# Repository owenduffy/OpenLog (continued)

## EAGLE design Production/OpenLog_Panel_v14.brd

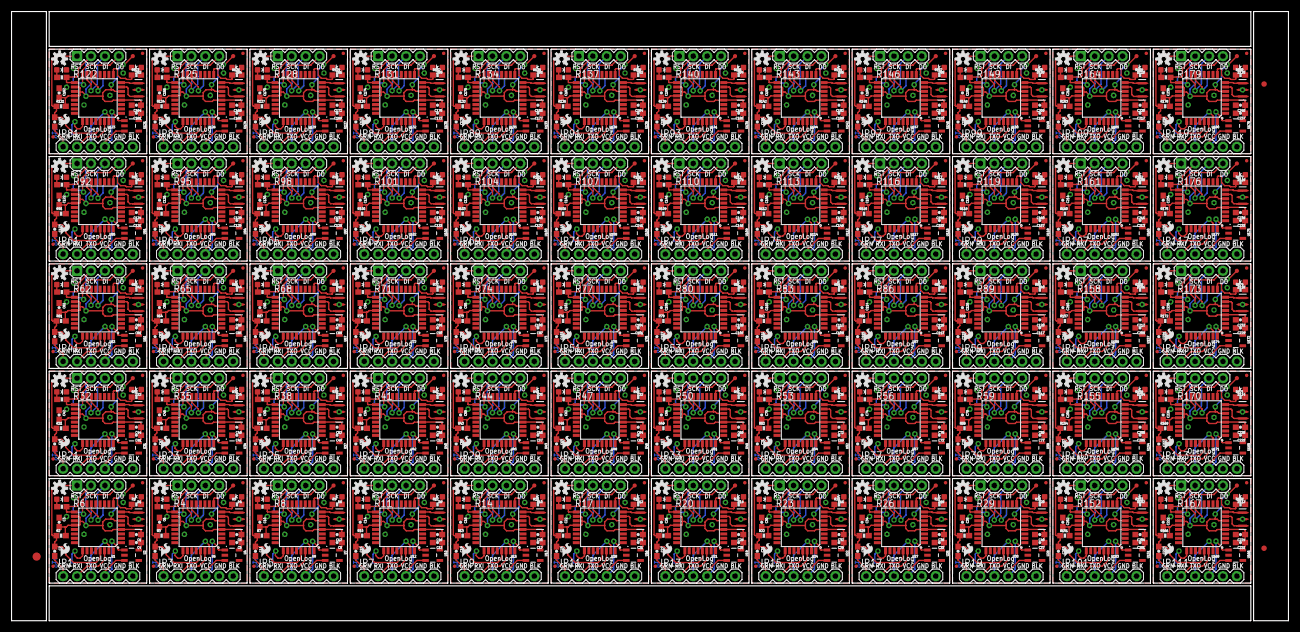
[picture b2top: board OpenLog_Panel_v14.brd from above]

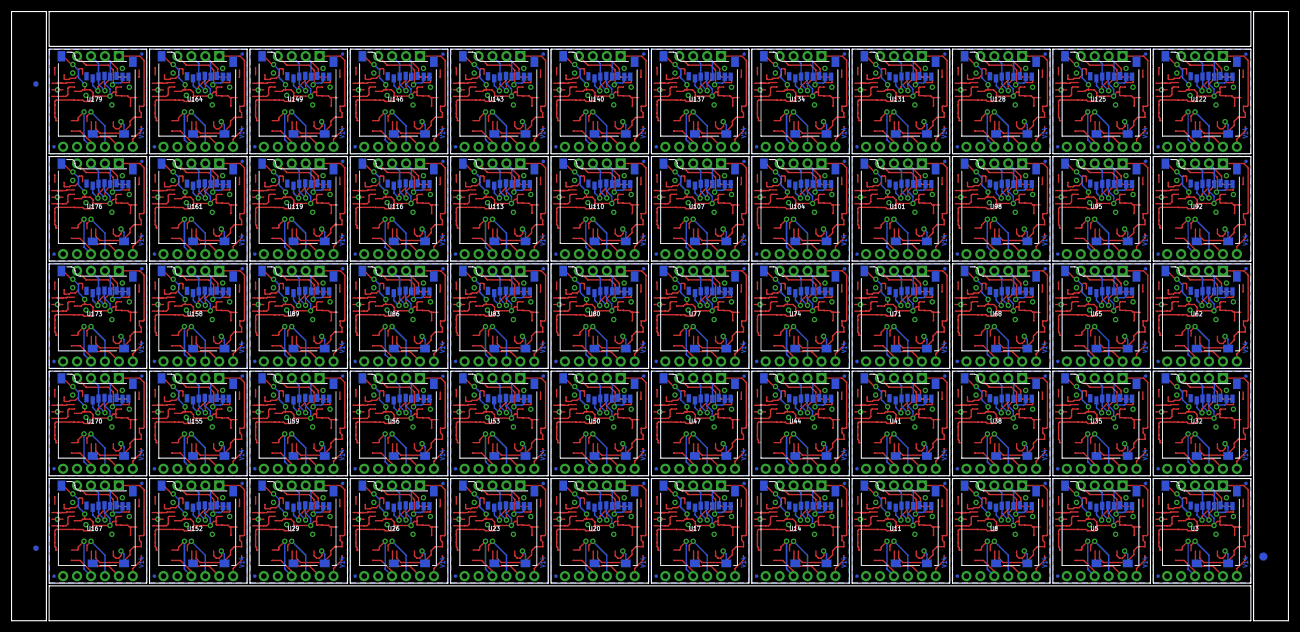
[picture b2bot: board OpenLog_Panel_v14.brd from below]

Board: 2 copper layers, 232.7 x 111.0 mm, 1326 parts (183 on the bottom side), 1020 nets.

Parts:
C1, C8, C12, C16, C20, C24, C28, C32, C36, C40, C44, C48, C52, C56, C60, C64, C68, C72, C76, C80, C84, C88, C92, C96, C100, C104, C108, C112, C116, C120, C124, C128, C132, C136, C140, C144, C148, C152, C156, C160, C164, C168, C172, C176, C180, C184, C188, C192, C196, C200, C204, C208, C212, C216, C220, C224, C228, C232, C236, C240: 1.0uF; 0603-CAP
C2, C3, C4, C5, C6, C7, C9, C10, C11, C13, C14, C15, C17, C18, C19, C21, C22, C23, C25, C26, C27, C29, C30, C31, C33, C34, C35, C37, C38, C39, C41, C42, C43, C45, C46, C47, C49, C50, C51, C53, C54, C55, C57, C58, C59, C61, C62, C63, C65, C66, C67, C69, C70, C71, C73, C74, C75, C77, C78, C79, C81, C82, C83, C85, C86, C87, C89, C90, C91, C93, C94, C95, C97, C98, C99, C101, C102, C103, C105, C106, C107, C109, C110, C111, C113, C114, C115, C117, C118, C119, C121, C122, C123, C125, C126, C127, C129, C130, C131, C133, C134, C135, C137, C138, C139, C141, C142, C143, C145, C146, C147, C149, C150, C151, C153, C154, C155, C157, C158, C159, C161, C162, C163, C165, C166, C167, C169, C170, C171, C173, C174, C175, C177, C178, C179, C181, C182, C183, C185, C186, C187, C189, C190, C191, C193, C194, C195, C197, C198, C199, C201, C202, C203, C205, C206, C207, C209, C210, C211, C213, C214, C215, C217, C218, C219, C221, C222, C223, C225, C226, C227, C229, C230, C231, C233, C234, C235, C237, C238, C239: 0.1uF; 0603-CAP
D1, D4, D6, D8, D10, D12, D14, D16, D18, D20, D22, D24, D26, D28, D30, D32, D34, D36, D38, D40, D42, D44, D46, D48, D50, D52, D54, D56, D58, D60, D62, D64, D66, D68, D70, D72, D74, D76, D78, D80, D82, D84, D86, D88, D90, D92, D94, D96, D98, D100, D102, D104, D106, D108, D110, D112, D114, D116, D118, D120: BLUE; LED-0603
D2, D3, D5, D7, D9, D11, D13, D15, D17, D19, D21, D23, D25, D27, D29, D31, D33, D35, D37, D39, D41, D43, D45, D47, D49, D51, D53, D55, D57, D59, D61, D63, D65, D67, D69, D71, D73, D75, D77, D79, D81, D83, D85, D87, D89, D91, D93, D95, D97, D99, D101, D103, D105, D107, D109, D111, D113, D115, D117, D119: GREEN; LED-0603
E$1, E$2: FIDUCIAL-1.5X3
E$3, E$4, E$6, E$7: FIDUCIAL-1X2
FID1, FID2, FID3, FID4, FID5, FID6, FID7, FID8, FID9, FID10, FID11, FID12, FID13, FID14, FID15, FID16, FID17, FID18, FID19, FID20, FID21, FID22, FID23, FID24, FID25, FID26, FID27, FID28, FID29, FID30, FID31, FID32, FID33, FID34, FID35, FID36, FID37, FID38, FID39, FID40, FID41, FID42, FID43, FID44, FID45, FID46, FID47, FID48, FID49, FID50, FID51, FID52, FID53, FID54, FID55, FID56, FID57, FID58, FID59, FID60, FID61, FID62, FID63, FID64, FID65, FID66, FID67, FID68, FID69, FID70, FID71, FID72, FID73, FID74, FID75, FID76, FID77, FID78, FID79, FID80, FID81, FID82, FID83, FID84, FID85, FID86, FID87, FID88, FID89, FID90, FID91, FID92, FID93, FID94, FID95, FID96, FID97, FID98, FID99, FID100, FID101, FID102, FID103, FID104, FID105, FID106, FID107, FID108, FID109, FID110, FID111, FID112, FID113, FID114, FID115, FID116, FID117, FID118, FID119, FID120, FID121, FID122, FID123, FID124, FID125, FID126, FID127, FID128, FID129, FID130, FID131, FID132, FID133, FID134, FID135, FID136, FID137, FID138, FID139, FID140, FID141, FID142, FID143, FID144, FID145, FID146, FID147, FID148, FID149, FID150, FID151, FID152, FID153, FID154, FID155, FID156, FID157, FID158, FID159, FID160, FID161, FID162, FID163, FID164, FID165, FID166, FID167, FID168, FID169, FID170, FID171, FID172, FID173, FID174, FID175, FID176, FID177, FID178, FID179, FID180, FID181, FID182, FID183, FID184, FID185, FID186, FID187, FID188, FID189, FID190, FID191, FID192, FID193, FID194, FID195, FID196, FID197, FID198, FID199, FID200, FID201, FID202, FID203, FID204, FID205, FID206, FID207, FID208, FID209, FID210, FID211, FID212, FID213, FID214, FID215, FID216, FID217, FID218, FID219, FID220, FID221, FID222, FID223, FID224, FID225, FID226, FID227, FID228, FID229, FID230, FID231, FID232, FID233, FID234, FID235, FID236, FID237, FID238, FID239, FID240: FIDUCIALUFIDUCIAL; MICRO-FIDUCIAL
JP1, JP3, JP5, JP7, JP9, JP11, JP13, JP15, JP17, JP19, JP21, JP23, JP25, JP27, JP29, JP31, JP33, JP35, JP37, JP39, JP41, JP43, JP45, JP47, JP49, JP51, JP53, JP55, JP57, JP59, JP61, JP63, JP65, JP67, JP69, JP71, JP73, JP75, JP77, JP79, JP81, JP83, JP85, JP87, JP89, JP91, JP93, JP95, JP97, JP99, JP101, JP103, JP105, JP107, JP109, JP111, JP113, JP115, JP117, JP119: Serial Connection; 1X06
JP2, JP4, JP6, JP8, JP10, JP12, JP14, JP16, JP18, JP20, JP22, JP24, JP26, JP28, JP30, JP32, JP34, JP36, JP38, JP40, JP42, JP44, JP46, JP48, JP50, JP52, JP54, JP56, JP58, JP60, JP62, JP64, JP66, JP68, JP70, JP72, JP74, JP76, JP78, JP80, JP82, JP84, JP86, JP88, JP90, JP92, JP94, JP96, JP98, JP100, JP102, JP104, JP106, JP108, JP110, JP112, JP114, JP116, JP118, JP120: 1X04
LOGO1, LOGO3, LOGO5, LOGO7, LOGO9, LOGO11, LOGO13, LOGO15, LOGO17, LOGO19, LOGO21, LOGO23, LOGO25, LOGO27, LOGO29, LOGO31, LOGO33, LOGO35, LOGO37, LOGO39, LOGO41, LOGO43, LOGO45, LOGO47, LOGO49, LOGO51, LOGO53, LOGO55, LOGO57, LOGO59, LOGO61, LOGO63, LOGO65, LOGO67, LOGO69, LOGO71, LOGO73, LOGO75, LOGO77, LOGO79, LOGO81, LOGO83, LOGO85, LOGO87, LOGO89, LOGO91, LOGO93, LOGO95, LOGO97, LOGO99, LOGO101, LOGO103, LOGO105, LOGO107, LOGO109, LOGO111, LOGO113, LOGO115, LOGO117, LOGO119: SFE_LOGO_FLAME.1_INCH; SFE_LOGO_FLAME_.1
LOGO2, LOGO4, LOGO6, LOGO8, LOGO10, LOGO12, LOGO14, LOGO16, LOGO18, LOGO20, LOGO22, LOGO24, LOGO26, LOGO28, LOGO30, LOGO32, LOGO34, LOGO36, LOGO38, LOGO40, LOGO42, LOGO44, LOGO46, LOGO48, LOGO50, LOGO52, LOGO54, LOGO56, LOGO58, LOGO60, LOGO62, LOGO64, LOGO66, LOGO68, LOGO70, LOGO72, LOGO74, LOGO76, LOGO78, LOGO80, LOGO82, LOGO84, LOGO86, LOGO88, LOGO90, LOGO92, LOGO94, LOGO96, LOGO98, LOGO100, LOGO102, LOGO104, LOGO106, LOGO108, LOGO110, LOGO112, LOGO114, LOGO116, LOGO118, LOGO120: OSHW-LOGOS; OSHW-LOGO-S
Q1, Q2, Q3, Q4, Q5, Q6, Q7, Q8, Q9, Q10, Q11, Q12, Q13, Q14, Q15, Q16, Q17, Q18, Q19, Q20, Q21, Q22, Q23, Q24, Q25, Q26, Q27, Q28, Q29, Q30, Q31, Q32, Q33, Q34, Q35, Q36, Q37, Q38, Q39, Q40, Q41, Q42, Q43, Q44, Q45, Q46, Q47, Q48, Q49, Q50, Q51, Q52, Q53, Q54, Q55, Q56, Q57, Q58, Q59, Q60: 16MHZ; RESONATOR-SMD
R1, R4, R5, R6, R8, R9, R11, R12, R14, R15, R17, R18, R20, R21, R23, R24, R26, R27, R29, R30, R32, R33, R35, R36, R38, R39, R41, R42, R44, R45, R47, R48, R50, R51, R53, R54, R56, R57, R59, R60, R62, R63, R65, R66, R68, R69, R71, R72, R74, R75, R77, R78, R80, R81, R83, R84, R86, R87, R89, R90, R92, R93, R95, R96, R98, R99, R101, R102, R104, R105, R107, R108, R110, R111, R113, R114, R116, R117, R119, R120, R122, R123, R125, R126, R128, R129, R131, R132, R134, R135, R137, R138, R140, R141, R143, R144, R146, R147, R149, R150, R152, R153, R155, R156, R158, R159, R161, R162, R164, R165, R167, R168, R170, R171, R173, R174, R176, R177, R179, R180: 1K; 0603-RES
R2, R3, R7, R10, R13, R16, R19, R22, R25, R28, R31, R34, R37, R40, R43, R46, R49, R52, R55, R58, R61, R64, R67, R70, R73, R76, R79, R82, R85, R88, R91, R94, R97, R100, R103, R106, R109, R112, R115, R118, R121, R124, R127, R130, R133, R136, R139, R142, R145, R148, R151, R154, R157, R160, R163, R166, R169, R172, R175, R178: 10K; 0603-RES
TP1, TP2, TP3, TP4, TP5, TP6, TP7, TP8, TP9, TP10, TP11, TP12, TP13, TP14, TP15, TP16, TP17, TP18, TP19, TP20, TP21, TP22, TP23, TP24, TP25, TP26, TP27, TP28, TP29, TP30, TP31, TP32, TP33, TP34, TP35, TP36, TP37, TP38, TP39, TP40, TP41, TP42, TP43, TP44, TP45, TP46, TP47, TP48, TP49, TP50, TP51, TP52, TP53, TP54, TP55, TP56, TP57, TP58, TP59, TP60: TEST-POINT3; PAD.03X.03
U1, U6, U9, U12, U15, U18, U21, U24, U27, U30, U33, U36, U39, U42, U45, U48, U51, U54, U57, U60, U63, U66, U69, U72, U75, U78, U81, U84, U87, U90, U93, U96, U99, U102, U105, U108, U111, U114, U117, U120, U123, U126, U129, U132, U135, U138, U141, U144, U147, U150, U153, U156, U159, U162, U165, U168, U171, U174, U177, U180: ATMEGA328P_TQFP; TQFP32-08
U2, U4, U7, U10, U13, U16, U19, U22, U25, U28, U31, U34, U37, U40, U43, U46, U49, U52, U55, U58, U61, U64, U67, U70, U73, U76, U79, U82, U85, U88, U91, U94, U97, U100, U103, U106, U109, U112, U115, U118, U121, U124, U127, U130, U133, U136, U139, U142, U145, U148, U151, U154, U157, U160, U163, U166, U169, U172, U175, U178: 3.3V MIC5205; SOT23-5
U3, U5, U8, U11, U14, U17, U20, U23, U26, U29, U32, U35, U38, U41, U44, U47, U50, U53, U56, U59, U62, U65, U68, U71, U74, U77, U80, U83, U86, U89, U92, U95, U98, U101, U104, U107, U110, U113, U116, U119, U122, U125, U128, U131, U134, U137, U140, U143, U146, U149, U152, U155, U158, U161, U164, U167, U170, U173, U176, U179: microSD Socket; MICROSD_1:1

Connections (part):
3.3V: C1.1, C3.2, C4.1, R2.2, TP1.P$1, U1.4, U1.6, U1.18, U1.20, U2.5, U3.4
3.3V1: C5.1, C6.2, C8.1, R3.2, TP2.P$1, U4.5, U5.4, U6.4, U6.6, U6.18, U6.20
3.3V2: C9.1, C10.2, C12.1, R7.2, TP3.P$1, U7.5, U8.4, U9.4, U9.6, U9.18, U9.20
3.3V3: C13.1, C14.2, C16.1, R10.2, TP4.P$1, U10.5, U11.4, U12.4, U12.6, U12.18, U12.20
3.3V4: C17.1, C18.2, C20.1, R13.2, TP5.P$1, U13.5, U14.4, U15.4, U15.6, U15.18, U15.20
3.3V5: C21.1, C22.2, C24.1, R16.2, TP6.P$1, U16.5, U17.4, U18.4, U18.6, U18.18, U18.20
3.3V6: C25.1, C26.2, C28.1, R19.2, TP7.P$1, U19.5, U20.4, U21.4, U21.6, U21.18, U21.20
3.3V7: C29.1, C30.2, C32.1, R22.2, TP8.P$1, U22.5, U23.4, U24.4, U24.6, U24.18, U24.20
3.3V8: C33.1, C34.2, C36.1, R25.2, TP9.P$1, U25.5, U26.4, U27.4, U27.6, U27.18, U27.20
3.3V9: C37.1, C38.2, C40.1, R28.2, TP10.P$1, U28.5, U29.4, U30.4, U30.6, U30.18, U30.20
3.3V10: C41.1, C42.2, C44.1, R31.2, TP11.P$1, U31.5, U32.4, U33.4, U33.6, U33.18, U33.20
3.3V11: C45.1, C46.2, C48.1, R34.2, TP12.P$1, U34.5, U35.4, U36.4, U36.6, U36.18, U36.20
3.3V12: C49.1, C50.2, C52.1, R37.2, TP13.P$1, U37.5, U38.4, U39.4, U39.6, U39.18, U39.20
3.3V13: C53.1, C54.2, C56.1, R40.2, TP14.P$1, U40.5, U41.4, U42.4, U42.6, U42.18, U42.20
3.3V14: C57.1, C58.2, C60.1, R43.2, TP15.P$1, U43.5, U44.4, U45.4, U45.6, U45.18, U45.20
3.3V15: C61.1, C62.2, C64.1, R46.2, TP16.P$1, U46.5, U47.4, U48.4, U48.6, U48.18, U48.20
3.3V16: C65.1, C66.2, C68.1, R49.2, TP17.P$1, U49.5, U50.4, U51.4, U51.6, U51.18, U51.20
3.3V17: C69.1, C70.2, C72.1, R52.2, TP18.P$1, U52.5, U53.4, U54.4, U54.6, U54.18, U54.20
3.3V18: C73.1, C74.2, C76.1, R55.2, TP19.P$1, U55.5, U56.4, U57.4, U57.6, U57.18, U57.20
3.3V19: C77.1, C78.2, C80.1, R58.2, TP20.P$1, U58.5, U59.4, U60.4, U60.6, U60.18, U60.20
3.3V20: C81.1, C82.2, C84.1, R61.2, TP21.P$1, U61.5, U62.4, U63.4, U63.6, U63.18, U63.20
3.3V21: C85.1, C86.2, C88.1, R64.2, TP22.P$1, U64.5, U65.4, U66.4, U66.6, U66.18, U66.20
3.3V22: C89.1, C90.2, C92.1, R67.2, TP23.P$1, U67.5, U68.4, U69.4, U69.6, U69.18, U69.20
3.3V23: C93.1, C94.2, C96.1, R70.2, TP24.P$1, U70.5, U71.4, U72.4, U72.6, U72.18, U72.20
3.3V24: C97.1, C98.2, C100.1, R73.2, TP25.P$1, U73.5, U74.4, U75.4, U75.6, U75.18, U75.20
3.3V25: C101.1, C102.2, C104.1, R76.2, TP26.P$1, U76.5, U77.4, U78.4, U78.6, U78.18, U78.20
3.3V26: C105.1, C106.2, C108.1, R79.2, TP27.P$1, U79.5, U80.4, U81.4, U81.6, U81.18, U81.20
3.3V27: C109.1, C110.2, C112.1, R82.2, TP28.P$1, U82.5, U83.4, U84.4, U84.6, U84.18, U84.20
3.3V28: C113.1, C114.2, C116.1, R85.2, TP29.P$1, U85.5, U86.4, U87.4, U87.6, U87.18, U87.20
3.3V29: C117.1, C118.2, C120.1, R88.2, TP30.P$1, U88.5, U89.4, U90.4, U90.6, U90.18, U90.20
3.3V30: C121.1, C122.2, C124.1, R91.2, TP31.P$1, U91.5, U92.4, U93.4, U93.6, U93.18, U93.20
3.3V31: C125.1, C126.2, C128.1, R94.2, TP32.P$1, U94.5, U95.4, U96.4, U96.6, U96.18, U96.20
3.3V32: C129.1, C130.2, C132.1, R97.2, TP33.P$1, U97.5, U98.4, U99.4, U99.6, U99.18, U99.20
3.3V33: C133.1, C134.2, C136.1, R100.2, TP34.P$1, U100.5, U101.4, U102.4, U102.6, U102.18, U102.20
3.3V34: C137.1, C138.2, C140.1, R103.2, TP35.P$1, U103.5, U104.4, U105.4, U105.6, U105.18, U105.20
3.3V35: C141.1, C142.2, C144.1, R106.2, TP36.P$1, U106.5, U107.4, U108.4, U108.6, U108.18, U108.20
3.3V36: C145.1, C146.2, C148.1, R109.2, TP37.P$1, U109.5, U110.4, U111.4, U111.6, U111.18, U111.20
3.3V37: C149.1, C150.2, C152.1, R112.2, TP38.P$1, U112.5, U113.4, U114.4, U114.6, U114.18, U114.20
3.3V38: C153.1, C154.2, C156.1, R115.2, TP39.P$1, U115.5, U116.4, U117.4, U117.6, U117.18, U117.20
3.3V39: C157.1, C158.2, C160.1, R118.2, TP40.P$1, U118.5, U119.4, U120.4, U120.6, U120.18, U120.20
3.3V40: C161.1, C162.2, C164.1, R121.2, TP41.P$1, U121.5, U122.4, U123.4, U123.6, U123.18, U123.20
3.3V41: C165.1, C166.2, C168.1, R124.2, TP42.P$1, U124.5, U125.4, U126.4, U126.6, U126.18, U126.20
3.3V42: C169.1, C170.2, C172.1, R127.2, TP43.P$1, U127.5, U128.4, U129.4, U129.6, U129.18, U129.20
3.3V43: C173.1, C174.2, C176.1, R130.2, TP44.P$1, U130.5, U131.4, U132.4, U132.6, U132.18, U132.20
3.3V44: C177.1, C178.2, C180.1, R133.2, TP45.P$1, U133.5, U134.4, U135.4, U135.6, U135.18, U135.20
3.3V45: C181.1, C182.2, C184.1, R136.2, TP46.P$1, U136.5, U137.4, U138.4, U138.6, U138.18, U138.20
3.3V46: C185.1, C186.2, C188.1, R139.2, TP47.P$1, U139.5, U140.4, U141.4, U141.6, U141.18, U141.20
3.3V47: C189.1, C190.2, C192.1, R142.2, TP48.P$1, U142.5, U143.4, U144.4, U144.6, U144.18, U144.20
3.3V48: C193.1, C194.2, C196.1, R145.2, TP49.P$1, U145.5, U146.4, U147.4, U147.6, U147.18, U147.20
3.3V49: C197.1, C198.2, C200.1, R148.2, TP50.P$1, U148.5, U149.4, U150.4, U150.6, U150.18, U150.20
3.3V50: C201.1, C202.2, C204.1, R151.2, TP51.P$1, U151.5, U152.4, U153.4, U153.6, U153.18, U153.20
3.3V51: C205.1, C206.2, C208.1, R154.2, TP52.P$1, U154.5, U155.4, U156.4, U156.6, U156.18, U156.20
3.3V52: C209.1, C210.2, C212.1, R157.2, TP53.P$1, U157.5, U158.4, U159.4, U159.6, U159.18, U159.20
3.3V53: C213.1, C214.2, C216.1, R160.2, TP54.P$1, U160.5, U161.4, U162.4, U162.6, U162.18, U162.20
3.3V54: C217.1, C218.2, C220.1, R163.2, TP55.P$1, U163.5, U164.4, U165.4, U165.6, U165.18, U165.20
3.3V55: C221.1, C222.2, C224.1, R166.2, TP56.P$1, U166.5, U167.4, U168.4, U168.6, U168.18, U168.20
3.3V56: C225.1, C226.2, C228.1, R169.2, TP57.P$1, U169.5, U170.4, U171.4, U171.6, U171.18, U171.20
3.3V57: C229.1, C230.2, C232.1, R172.2, TP58.P$1, U172.5, U173.4, U174.4, U174.6, U174.18, U174.20
3.3V58: C233.1, C234.2, C236.1, R175.2, TP59.P$1, U175.5, U176.4, U177.4, U177.6, U177.18, U177.20
3.3V59: C237.1, C238.2, C240.1, R178.2, TP60.P$1, U178.5, U179.4, U180.4, U180.6, U180.18, U180.20
CD: U1.25, U3.CD1
CD1: U5.CD1, U6.25
CD2: U8.CD1, U9.25
CD3: U11.CD1, U12.25
CD4: U14.CD1, U15.25
CD5: U17.CD1, U18.25
CD6: U20.CD1, U21.25
CD7: U23.CD1, U24.25
CD8: U26.CD1, U27.25
CD9: U29.CD1, U30.25
CD10: U32.CD1, U33.25
CD11: U35.CD1, U36.25
CD12: U38.CD1, U39.25
CD13: U41.CD1, U42.25
CD14: U44.CD1, U45.25
CD15: U47.CD1, U48.25
CD16: U50.CD1, U51.25
CD17: U53.CD1, U54.25
CD18: U56.CD1, U57.25
CD19: U59.CD1, U60.25
CD20: U62.CD1, U63.25
CD21: U65.CD1, U66.25
CD22: U68.CD1, U69.25
CD23: U71.CD1, U72.25
CD24: U74.CD1, U75.25
CD25: U77.CD1, U78.25
CD26: U80.CD1, U81.25
CD27: U83.CD1, U84.25
CD28: U86.CD1, U87.25
CD29: U89.CD1, U90.25
CD30: U92.CD1, U93.25
CD31: U95.CD1, U96.25
CD32: U98.CD1, U99.25
CD33: U101.CD1, U102.25
CD34: U104.CD1, U105.25
CD35: U107.CD1, U108.25
CD36: U110.CD1, U111.25
CD37: U113.CD1, U114.25
CD38: U116.CD1, U117.25
CD39: U119.CD1, U120.25
CD40: U122.CD1, U123.25
CD41: U125.CD1, U126.25
CD42: U128.CD1, U129.25
CD43: U131.CD1, U132.25
CD44: U134.CD1, U135.25
CD45: U137.CD1, U138.25
CD46: U140.CD1, U141.25
CD47: U143.CD1, U144.25
CD48: U146.CD1, U147.25
CD49: U149.CD1, U150.25
CD50: U152.CD1, U153.25
CD51: U155.CD1, U156.25
CD52: U158.CD1, U159.25
CD53: U161.CD1, U162.25
CD54: U164.CD1, U165.25
CD55: U167.CD1, U168.25
CD56: U170.CD1, U171.25
CD57: U173.CD1, U174.25
CD58: U176.CD1, U177.25
CD59: U179.CD1, U180.25
CS: U1.14, U3.2
CS1: U5.2, U6.14
CS2: U8.2, U9.14
CS3: U11.2, U12.14
CS4: U14.2, U15.14
CS5: U17.2, U18.14
CS6: U20.2, U21.14
CS7: U23.2, U24.14
CS8: U26.2, U27.14
CS9: U29.2, U30.14
CS10: U32.2, U33.14
CS11: U35.2, U36.14
CS12: U38.2, U39.14
CS13: U41.2, U42.14
CS14: U44.2, U45.14
CS15: U47.2, U48.14
CS16: U50.2, U51.14
CS17: U53.2, U54.14
CS18: U56.2, U57.14
CS19: U59.2, U60.14
CS20: U62.2, U63.14
CS21: U65.2, U66.14
CS22: U68.2, U69.14
CS23: U71.2, U72.14
CS24: U74.2, U75.14
CS25: U77.2, U78.14
CS26: U80.2, U81.14
CS27: U83.2, U84.14
CS28: U86.2, U87.14
CS29: U89.2, U90.14
CS30: U92.2, U93.14
CS31: U95.2, U96.14
CS32: U98.2, U99.14
CS33: U101.2, U102.14
CS34: U104.2, U105.14
CS35: U107.2, U108.14
CS36: U110.2, U111.14
CS37: U113.2, U114.14
CS38: U116.2, U117.14
CS39: U119.2, U120.14
CS40: U122.2, U123.14
CS41: U125.2, U126.14
CS42: U128.2, U129.14
CS43: U131.2, U132.14
CS44: U134.2, U135.14
CS45: U137.2, U138.14
CS46: U140.2, U141.14
CS47: U143.2, U144.14
CS48: U146.2, U147.14
CS49: U149.2, U150.14
CS50: U152.2, U153.14
CS51: U155.2, U156.14
CS52: U158.2, U159.14
CS53: U161.2, U162.14
CS54: U164.2, U165.14
CS55: U167.2, U168.14
CS56: U170.2, U171.14
CS57: U173.2, U174.14
CS58: U176.2, U177.14
CS59: U179.2, U180.14
DTR: C2.2, JP1.1
DTR1: C7.2, JP3.1
DTR2: C11.2, JP5.1
DTR3: C15.2, JP7.1
DTR4: C19.2, JP9.1
DTR5: C23.2, JP11.1
DTR6: C27.2, JP13.1
DTR7: C31.2, JP15.1
DTR8: C35.2, JP17.1
DTR9: C39.2, JP19.1
DTR10: C43.2, JP21.1
DTR11: C47.2, JP23.1
DTR12: C51.2, JP25.1
DTR13: C55.2, JP27.1
DTR14: C59.2, JP29.1
DTR15: C63.2, JP31.1
DTR16: C67.2, JP33.1
DTR17: C71.2, JP35.1
DTR18: C75.2, JP37.1
DTR19: C79.2, JP39.1
DTR20: C83.2, JP41.1
DTR21: C87.2, JP43.1
DTR22: C91.2, JP45.1
DTR23: C95.2, JP47.1
DTR24: C99.2, JP49.1
DTR25: C103.2, JP51.1
DTR26: C107.2, JP53.1
DTR27: C111.2, JP55.1
DTR28: C115.2, JP57.1
DTR29: C119.2, JP59.1
DTR30: C123.2, JP61.1
DTR31: C127.2, JP63.1
DTR32: C131.2, JP65.1
DTR33: C135.2, JP67.1
DTR34: C139.2, JP69.1
DTR35: C143.2, JP71.1
DTR36: C147.2, JP73.1
DTR37: C151.2, JP75.1
DTR38: C155.2, JP77.1
DTR39: C159.2, JP79.1
DTR40: C163.2, JP81.1
DTR41: C167.2, JP83.1
DTR42: C171.2, JP85.1
DTR43: C175.2, JP87.1
DTR44: C179.2, JP89.1
DTR45: C183.2, JP91.1
DTR46: C187.2, JP93.1
DTR47: C191.2, JP95.1
DTR48: C195.2, JP97.1
DTR49: C199.2, JP99.1
DTR50: C203.2, JP101.1
DTR51: C207.2, JP103.1
DTR52: C211.2, JP105.1
DTR53: C215.2, JP107.1
DTR54: C219.2, JP109.1
DTR55: C223.2, JP111.1
DTR56: C227.2, JP113.1
DTR57: C231.2, JP115.1
DTR58: C235.2, JP117.1
DTR59: C239.2, JP119.1
GND: C1.2, C3.1, C4.2, D1.C, D3.C, JP1.5, JP1.6, Q1.2, U1.3, U1.5, U1.21, U2.2, U3.6, U3.GND1, U3.GND3
GND1: C5.2, C6.1, C8.2, D2.C, D4.C, JP3.5, JP3.6, Q2.2, U4.2, U5.6, U5.GND1, U5.GND3, U6.3, U6.5, U6.21
GND2: C9.2, C10.1, C12.2, D5.C, D6.C, JP5.5, JP5.6, Q3.2, U7.2, U8.6, U8.GND1, U8.GND3, U9.3, U9.5, U9.21
GND3: C13.2, C14.1, C16.2, D7.C, D8.C, JP7.5, JP7.6, Q4.2, U10.2, U11.6, U11.GND1, U11.GND3, U12.3, U12.5, U12.21
GND4: C17.2, C18.1, C20.2, D9.C, D10.C, JP9.5, JP9.6, Q5.2, U13.2, U14.6, U14.GND1, U14.GND3, U15.3, U15.5, U15.21
GND5: C21.2, C22.1, C24.2, D11.C, D12.C, JP11.5, JP11.6, Q6.2, U16.2, U17.6, U17.GND1, U17.GND3, U18.3, U18.5, U18.21
GND6: C25.2, C26.1, C28.2, D13.C, D14.C, JP13.5, JP13.6, Q7.2, U19.2, U20.6, U20.GND1, U20.GND3, U21.3, U21.5, U21.21
GND7: C29.2, C30.1, C32.2, D15.C, D16.C, JP15.5, JP15.6, Q8.2, U22.2, U23.6, U23.GND1, U23.GND3, U24.3, U24.5, U24.21
GND8: C33.2, C34.1, C36.2, D17.C, D18.C, JP17.5, JP17.6, Q9.2, U25.2, U26.6, U26.GND1, U26.GND3, U27.3, U27.5, U27.21
GND9: C37.2, C38.1, C40.2, D19.C, D20.C, JP19.5, JP19.6, Q10.2, U28.2, U29.6, U29.GND1, U29.GND3, U30.3, U30.5, U30.21
GND10: C41.2, C42.1, C44.2, D21.C, D22.C, JP21.5, JP21.6, Q11.2, U31.2, U32.6, U32.GND1, U32.GND3, U33.3, U33.5, U33.21
GND11: C45.2, C46.1, C48.2, D23.C, D24.C, JP23.5, JP23.6, Q12.2, U34.2, U35.6, U35.GND1, U35.GND3, U36.3, U36.5, U36.21
GND12: C49.2, C50.1, C52.2, D25.C, D26.C, JP25.5, JP25.6, Q13.2, U37.2, U38.6, U38.GND1, U38.GND3, U39.3, U39.5, U39.21
GND13: C53.2, C54.1, C56.2, D27.C, D28.C, JP27.5, JP27.6, Q14.2, U40.2, U41.6, U41.GND1, U41.GND3, U42.3, U42.5, U42.21
GND14: C57.2, C58.1, C60.2, D29.C, D30.C, JP29.5, JP29.6, Q15.2, U43.2, U44.6, U44.GND1, U44.GND3, U45.3, U45.5, U45.21
GND15: C61.2, C62.1, C64.2, D31.C, D32.C, JP31.5, JP31.6, Q16.2, U46.2, U47.6, U47.GND1, U47.GND3, U48.3, U48.5, U48.21
GND16: C65.2, C66.1, C68.2, D33.C, D34.C, JP33.5, JP33.6, Q17.2, U49.2, U50.6, U50.GND1, U50.GND3, U51.3, U51.5, U51.21
GND17: C69.2, C70.1, C72.2, D35.C, D36.C, JP35.5, JP35.6, Q18.2, U52.2, U53.6, U53.GND1, U53.GND3, U54.3, U54.5, U54.21
GND18: C73.2, C74.1, C76.2, D37.C, D38.C, JP37.5, JP37.6, Q19.2, U55.2, U56.6, U56.GND1, U56.GND3, U57.3, U57.5, U57.21
GND19: C77.2, C78.1, C80.2, D39.C, D40.C, JP39.5, JP39.6, Q20.2, U58.2, U59.6, U59.GND1, U59.GND3, U60.3, U60.5, U60.21
GND20: C81.2, C82.1, C84.2, D41.C, D42.C, JP41.5, JP41.6, Q21.2, U61.2, U62.6, U62.GND1, U62.GND3, U63.3, U63.5, U63.21
GND21: C85.2, C86.1, C88.2, D43.C, D44.C, JP43.5, JP43.6, Q22.2, U64.2, U65.6, U65.GND1, U65.GND3, U66.3, U66.5, U66.21
GND22: C89.2, C90.1, C92.2, D45.C, D46.C, JP45.5, JP45.6, Q23.2, U67.2, U68.6, U68.GND1, U68.GND3, U69.3, U69.5, U69.21
GND23: C93.2, C94.1, C96.2, D47.C, D48.C, JP47.5, JP47.6, Q24.2, U70.2, U71.6, U71.GND1, U71.GND3, U72.3, U72.5, U72.21
GND24: C97.2, C98.1, C100.2, D49.C, D50.C, JP49.5, JP49.6, Q25.2, U73.2, U74.6, U74.GND1, U74.GND3, U75.3, U75.5, U75.21
GND25: C101.2, C102.1, C104.2, D51.C, D52.C, JP51.5, JP51.6, Q26.2, U76.2, U77.6, U77.GND1, U77.GND3, U78.3, U78.5, U78.21
GND26: C105.2, C106.1, C108.2, D53.C, D54.C, JP53.5, JP53.6, Q27.2, U79.2, U80.6, U80.GND1, U80.GND3, U81.3, U81.5, U81.21
GND27: C109.2, C110.1, C112.2, D55.C, D56.C, JP55.5, JP55.6, Q28.2, U82.2, U83.6, U83.GND1, U83.GND3, U84.3, U84.5, U84.21
GND28: C113.2, C114.1, C116.2, D57.C, D58.C, JP57.5, JP57.6, Q29.2, U85.2, U86.6, U86.GND1, U86.GND3, U87.3, U87.5, U87.21
GND29: C117.2, C118.1, C120.2, D59.C, D60.C, JP59.5, JP59.6, Q30.2, U88.2, U89.6, U89.GND1, U89.GND3, U90.3, U90.5, U90.21
GND30: C121.2, C122.1, C124.2, D61.C, D62.C, JP61.5, JP61.6, Q31.2, U91.2, U92.6, U92.GND1, U92.GND3, U93.3, U93.5, U93.21
GND31: C125.2, C126.1, C128.2, D63.C, D64.C, JP63.5, JP63.6, Q32.2, U94.2, U95.6, U95.GND1, U95.GND3, U96.3, U96.5, U96.21
GND32: C129.2, C130.1, C132.2, D65.C, D66.C, JP65.5, JP65.6, Q33.2, U97.2, U98.6, U98.GND1, U98.GND3, U99.3, U99.5, U99.21
GND33: C133.2, C134.1, C136.2, D67.C, D68.C, JP67.5, JP67.6, Q34.2, U100.2, U101.6, U101.GND1, U101.GND3, U102.3, U102.5, U102.21
GND34: C137.2, C138.1, C140.2, D69.C, D70.C, JP69.5, JP69.6, Q35.2, U103.2, U104.6, U104.GND1, U104.GND3, U105.3, U105.5, U105.21
GND35: C141.2, C142.1, C144.2, D71.C, D72.C, JP71.5, JP71.6, Q36.2, U106.2, U107.6, U107.GND1, U107.GND3, U108.3, U108.5, U108.21
GND36: C145.2, C146.1, C148.2, D73.C, D74.C, JP73.5, JP73.6, Q37.2, U109.2, U110.6, U110.GND1, U110.GND3, U111.3, U111.5, U111.21
GND37: C149.2, C150.1, C152.2, D75.C, D76.C, JP75.5, JP75.6, Q38.2, U112.2, U113.6, U113.GND1, U113.GND3, U114.3, U114.5, U114.21
GND38: C153.2, C154.1, C156.2, D77.C, D78.C, JP77.5, JP77.6, Q39.2, U115.2, U116.6, U116.GND1, U116.GND3, U117.3, U117.5, U117.21
GND39: C157.2, C158.1, C160.2, D79.C, D80.C, JP79.5, JP79.6, Q40.2, U118.2, U119.6, U119.GND1, U119.GND3, U120.3, U120.5, U120.21
GND40: C161.2, C162.1, C164.2, D81.C, D82.C, JP81.5, JP81.6, Q41.2, U121.2, U122.6, U122.GND1, U122.GND3, U123.3, U123.5, U123.21
GND41: C165.2, C166.1, C168.2, D83.C, D84.C, JP83.5, JP83.6, Q42.2, U124.2, U125.6, U125.GND1, U125.GND3, U126.3, U126.5, U126.21
GND42: C169.2, C170.1, C172.2, D85.C, D86.C, JP85.5, JP85.6, Q43.2, U127.2, U128.6, U128.GND1, U128.GND3, U129.3, U129.5, U129.21
GND43: C173.2, C174.1, C176.2, D87.C, D88.C, JP87.5, JP87.6, Q44.2, U130.2, U131.6, U131.GND1, U131.GND3, U132.3, U132.5, U132.21
GND44: C177.2, C178.1, C180.2, D89.C, D90.C, JP89.5, JP89.6, Q45.2, U133.2, U134.6, U134.GND1, U134.GND3, U135.3, U135.5, U135.21
GND45: C181.2, C182.1, C184.2, D91.C, D92.C, JP91.5, JP91.6, Q46.2, U136.2, U137.6, U137.GND1, U137.GND3, U138.3, U138.5, U138.21
GND46: C185.2, C186.1, C188.2, D93.C, D94.C, JP93.5, JP93.6, Q47.2, U139.2, U140.6, U140.GND1, U140.GND3, U141.3, U141.5, U141.21
GND47: C189.2, C190.1, C192.2, D95.C, D96.C, JP95.5, JP95.6, Q48.2, U142.2, U143.6, U143.GND1, U143.GND3, U144.3, U144.5, U144.21
GND48: C193.2, C194.1, C196.2, D97.C, D98.C, JP97.5, JP97.6, Q49.2, U145.2, U146.6, U146.GND1, U146.GND3, U147.3, U147.5, U147.21
GND49: C197.2, C198.1, C200.2, D99.C, D100.C, JP99.5, JP99.6, Q50.2, U148.2, U149.6, U149.GND1, U149.GND3, U150.3, U150.5, U150.21
GND50: C201.2, C202.1, C204.2, D101.C, D102.C, JP101.5, JP101.6, Q51.2, U151.2, U152.6, U152.GND1, U152.GND3, U153.3, U153.5, U153.21
GND51: C205.2, C206.1, C208.2, D103.C, D104.C, JP103.5, JP103.6, Q52.2, U154.2, U155.6, U155.GND1, U155.GND3, U156.3, U156.5, U156.21
GND52: C209.2, C210.1, C212.2, D105.C, D106.C, JP105.5, JP105.6, Q53.2, U157.2, U158.6, U158.GND1, U158.GND3, U159.3, U159.5, U159.21
GND53: C213.2, C214.1, C216.2, D107.C, D108.C, JP107.5, JP107.6, Q54.2, U160.2, U161.6, U161.GND1, U161.GND3, U162.3, U162.5, U162.21
GND54: C217.2, C218.1, C220.2, D109.C, D110.C, JP109.5, JP109.6, Q55.2, U163.2, U164.6, U164.GND1, U164.GND3, U165.3, U165.5, U165.21
GND55: C221.2, C222.1, C224.2, D111.C, D112.C, JP111.5, JP111.6, Q56.2, U166.2, U167.6, U167.GND1, U167.GND3, U168.3, U168.5, U168.21
GND56: C225.2, C226.1, C228.2, D113.C, D114.C, JP113.5, JP113.6, Q57.2, U169.2, U170.6, U170.GND1, U170.GND3, U171.3, U171.5, U171.21
GND57: C229.2, C230.1, C232.2, D115.C, D116.C, JP115.5, JP115.6, Q58.2, U172.2, U173.6, U173.GND1, U173.GND3, U174.3, U174.5, U174.21
GND58: C233.2, C234.1, C236.2, D117.C, D118.C, JP117.5, JP117.6, Q59.2, U175.2, U176.6, U176.GND1, U176.GND3, U177.3, U177.5, U177.21
GND59: C237.2, C238.1, C240.2, D119.C, D120.C, JP119.5, JP119.6, Q60.2, U178.2, U179.6, U179.GND1, U179.GND3, U180.3, U180.5, U180.21
MISO: JP2.4, U1.16, U3.7
MISO1: JP4.4, U5.7, U6.16
MISO2: JP6.4, U8.7, U9.16
MISO3: JP8.4, U11.7, U12.16
MISO4: JP10.4, U14.7, U15.16
MISO5: JP12.4, U17.7, U18.16
MISO6: JP14.4, U20.7, U21.16
MISO7: JP16.4, U23.7, U24.16
MISO8: JP18.4, U26.7, U27.16
MISO9: JP20.4, U29.7, U30.16
MISO10: JP22.4, U32.7, U33.16
MISO11: JP24.4, U35.7, U36.16
MISO12: JP26.4, U38.7, U39.16
MISO13: JP28.4, U41.7, U42.16
MISO14: JP30.4, U44.7, U45.16
MISO15: JP32.4, U47.7, U48.16
MISO16: JP34.4, U50.7, U51.16
MISO17: JP36.4, U53.7, U54.16
MISO18: JP38.4, U56.7, U57.16
MISO19: JP40.4, U59.7, U60.16
MISO20: JP42.4, U62.7, U63.16
MISO21: JP44.4, U65.7, U66.16
MISO22: JP46.4, U68.7, U69.16
MISO23: JP48.4, U71.7, U72.16
MISO24: JP50.4, U74.7, U75.16
MISO25: JP52.4, U77.7, U78.16
MISO26: JP54.4, U80.7, U81.16
MISO27: JP56.4, U83.7, U84.16
MISO28: JP58.4, U86.7, U87.16
MISO29: JP60.4, U89.7, U90.16
MISO30: JP62.4, U92.7, U93.16
MISO31: JP64.4, U95.7, U96.16
MISO32: JP66.4, U98.7, U99.16
MISO33: JP68.4, U101.7, U102.16
MISO34: JP70.4, U104.7, U105.16
MISO35: JP72.4, U107.7, U108.16
MISO36: JP74.4, U110.7, U111.16
MISO37: JP76.4, U113.7, U114.16
MISO38: JP78.4, U116.7, U117.16
MISO39: JP80.4, U119.7, U120.16
MISO40: JP82.4, U122.7, U123.16
MISO41: JP84.4, U125.7, U126.16
MISO42: JP86.4, U128.7, U129.16
MISO43: JP88.4, U131.7, U132.16
MISO44: JP90.4, U134.7, U135.16
MISO45: JP92.4, U137.7, U138.16
MISO46: JP94.4, U140.7, U141.16
MISO47: JP96.4, U143.7, U144.16
MISO48: JP98.4, U146.7, U147.16
MISO49: JP100.4, U149.7, U150.16
MISO50: JP102.4, U152.7, U153.16
MISO51: JP104.4, U155.7, U156.16
MISO52: JP106.4, U158.7, U159.16
MISO53: JP108.4, U161.7, U162.16
MISO54: JP110.4, U164.7, U165.16
MISO55: JP112.4, U167.7, U168.16
MISO56: JP114.4, U170.7, U171.16
MISO57: JP116.4, U173.7, U174.16
MISO58: JP118.4, U176.7, U177.16
MISO59: JP120.4, U179.7, U180.16
MOSI: JP2.3, U1.15, U3.3
MOSI1: JP4.3, U5.3, U6.15
MOSI2: JP6.3, U8.3, U9.15
MOSI3: JP8.3, U11.3, U12.15
MOSI4: JP10.3, U14.3, U15.15
MOSI5: JP12.3, U17.3, U18.15
MOSI6: JP14.3, U20.3, U21.15
MOSI7: JP16.3, U23.3, U24.15
MOSI8: JP18.3, U26.3, U27.15
MOSI9: JP20.3, U29.3, U30.15
MOSI10: JP22.3, U32.3, U33.15
MOSI11: JP24.3, U35.3, U36.15
MOSI12: JP26.3, U38.3, U39.15
MOSI13: JP28.3, U41.3, U42.15
MOSI14: JP30.3, U44.3, U45.15
MOSI15: JP32.3, U47.3, U48.15
MOSI16: JP34.3, U50.3, U51.15
MOSI17: JP36.3, U53.3, U54.15
MOSI18: JP38.3, U56.3, U57.15
MOSI19: JP40.3, U59.3, U60.15
MOSI20: JP42.3, U62.3, U63.15
MOSI21: JP44.3, U65.3, U66.15
MOSI22: JP46.3, U68.3, U69.15
MOSI23: JP48.3, U71.3, U72.15
MOSI24: JP50.3, U74.3, U75.15
MOSI25: JP52.3, U77.3, U78.15
MOSI26: JP54.3, U80.3, U81.15
MOSI27: JP56.3, U83.3, U84.15
MOSI28: JP58.3, U86.3, U87.15
MOSI29: JP60.3, U89.3, U90.15
MOSI30: JP62.3, U92.3, U93.15
MOSI31: JP64.3, U95.3, U96.15
MOSI32: JP66.3, U98.3, U99.15
MOSI33: JP68.3, U101.3, U102.15
MOSI34: JP70.3, U104.3, U105.15
MOSI35: JP72.3, U107.3, U108.15
MOSI36: JP74.3, U110.3, U111.15
MOSI37: JP76.3, U113.3, U114.15
MOSI38: JP78.3, U116.3, U117.15
MOSI39: JP80.3, U119.3, U120.15
MOSI40: JP82.3, U122.3, U123.15
MOSI41: JP84.3, U125.3, U126.15
MOSI42: JP86.3, U128.3, U129.15
MOSI43: JP88.3, U131.3, U132.15
MOSI44: JP90.3, U134.3, U135.15
MOSI45: JP92.3, U137.3, U138.15
MOSI46: JP94.3, U140.3, U141.15
MOSI47: JP96.3, U143.3, U144.15
MOSI48: JP98.3, U146.3, U147.15
MOSI49: JP100.3, U149.3, U150.15
MOSI50: JP102.3, U152.3, U153.15
MOSI51: JP104.3, U155.3, U156.15
MOSI52: JP106.3, U158.3, U159.15
MOSI53: JP108.3, U161.3, U162.15
MOSI54: JP110.3, U164.3, U165.15
MOSI55: JP112.3, U167.3, U168.15
MOSI56: JP114.3, U170.3, U171.15
MOSI57: JP116.3, U173.3, U174.15
MOSI58: JP118.3, U176.3, U177.15
MOSI59: JP120.3, U179.3, U180.15
unnamed: Q1.1, U1.8
unnamed: Q1.3, U1.7
unnamed: D1.A, R1.2
unnamed: R1.1, U1.9
unnamed: D2.A, R4.2
unnamed: Q2.1, U6.8
unnamed: D3.A, R6.2
unnamed: Q2.3, U6.7
unnamed: D4.A, R5.2
unnamed: R5.1, U6.9
unnamed: D5.A, R8.2
unnamed: Q3.1, U9.8
unnamed: Q3.3, U9.7
unnamed: D6.A, R9.2
unnamed: R9.1, U9.9
unnamed: D7.A, R11.2
unnamed: Q4.1, U12.8
unnamed: Q4.3, U12.7
unnamed: D8.A, R12.2
unnamed: R12.1, U12.9
unnamed: D9.A, R14.2
unnamed: Q5.1, U15.8
unnamed: Q5.3, U15.7
unnamed: D10.A, R15.2
unnamed: R15.1, U15.9
unnamed: D11.A, R17.2
unnamed: Q6.1, U18.8
unnamed: Q6.3, U18.7
unnamed: D12.A, R18.2
unnamed: R18.1, U18.9
unnamed: D13.A, R20.2
unnamed: Q7.1, U21.8
unnamed: Q7.3, U21.7
unnamed: D14.A, R21.2
unnamed: R21.1, U21.9
unnamed: D15.A, R23.2
unnamed: Q8.1, U24.8
unnamed: Q8.3, U24.7
unnamed: D16.A, R24.2
unnamed: R24.1, U24.9
unnamed: D17.A, R26.2
unnamed: Q9.1, U27.8
unnamed: Q9.3, U27.7
unnamed: D18.A, R27.2
unnamed: R27.1, U27.9
unnamed: D19.A, R29.2
unnamed: Q10.1, U30.8
unnamed: Q10.3, U30.7
unnamed: D20.A, R30.2
unnamed: R30.1, U30.9
unnamed: D21.A, R32.2
unnamed: Q11.1, U33.8
unnamed: Q11.3, U33.7
unnamed: D22.A, R33.2
unnamed: R33.1, U33.9
unnamed: D23.A, R35.2
unnamed: Q12.1, U36.8
unnamed: Q12.3, U36.7
unnamed: D24.A, R36.2
unnamed: R36.1, U36.9
unnamed: D25.A, R38.2
unnamed: Q13.1, U39.8
unnamed: Q13.3, U39.7
unnamed: D26.A, R39.2
unnamed: R39.1, U39.9
unnamed: D27.A, R41.2
unnamed: Q14.1, U42.8
unnamed: Q14.3, U42.7
unnamed: D28.A, R42.2
unnamed: R42.1, U42.9
unnamed: D29.A, R44.2
unnamed: Q15.1, U45.8
unnamed: Q15.3, U45.7
unnamed: D30.A, R45.2
unnamed: R45.1, U45.9
unnamed: D31.A, R47.2
unnamed: Q16.1, U48.8
unnamed: Q16.3, U48.7
unnamed: D32.A, R48.2
unnamed: R48.1, U48.9
unnamed: D33.A, R50.2
unnamed: Q17.1, U51.8
unnamed: Q17.3, U51.7
unnamed: D34.A, R51.2
unnamed: R51.1, U51.9
unnamed: D35.A, R53.2
unnamed: Q18.1, U54.8
unnamed: Q18.3, U54.7
unnamed: D36.A, R54.2
unnamed: R54.1, U54.9
unnamed: D37.A, R56.2
unnamed: Q19.1, U57.8
unnamed: Q19.3, U57.7
unnamed: D38.A, R57.2
unnamed: R57.1, U57.9
unnamed: D39.A, R59.2
unnamed: Q20.1, U60.8
unnamed: Q20.3, U60.7
unnamed: D40.A, R60.2
unnamed: R60.1, U60.9
unnamed: D41.A, R62.2
unnamed: Q21.1, U63.8
unnamed: Q21.3, U63.7
unnamed: D42.A, R63.2
unnamed: R63.1, U63.9
unnamed: D43.A, R65.2
unnamed: Q22.1, U66.8
unnamed: Q22.3, U66.7
unnamed: D44.A, R66.2
unnamed: R66.1, U66.9
unnamed: D45.A, R68.2
unnamed: Q23.1, U69.8
unnamed: Q23.3, U69.7
unnamed: D46.A, R69.2
unnamed: R69.1, U69.9
unnamed: D47.A, R71.2
unnamed: Q24.1, U72.8
unnamed: Q24.3, U72.7
unnamed: D48.A, R72.2
unnamed: R72.1, U72.9
unnamed: D49.A, R74.2
unnamed: Q25.1, U75.8
unnamed: Q25.3, U75.7
unnamed: D50.A, R75.2
unnamed: R75.1, U75.9
unnamed: D51.A, R77.2
unnamed: Q26.1, U78.8
unnamed: Q26.3, U78.7
unnamed: D52.A, R78.2
unnamed: R78.1, U78.9
unnamed: D53.A, R80.2
unnamed: Q27.1, U81.8
unnamed: Q27.3, U81.7
unnamed: D54.A, R81.2
unnamed: R81.1, U81.9
unnamed: D55.A, R83.2
unnamed: Q28.1, U84.8
unnamed: Q28.3, U84.7
unnamed: D56.A, R84.2
unnamed: R84.1, U84.9
unnamed: D57.A, R86.2
unnamed: Q29.1, U87.8
unnamed: Q29.3, U87.7
unnamed: D58.A, R87.2
unnamed: R87.1, U87.9
unnamed: D59.A, R89.2
unnamed: Q30.1, U90.8
unnamed: Q30.3, U90.7
unnamed: D60.A, R90.2
unnamed: R90.1, U90.9
unnamed: D61.A, R92.2
unnamed: Q31.1, U93.8
unnamed: Q31.3, U93.7
unnamed: D62.A, R93.2
unnamed: R93.1, U93.9
unnamed: D63.A, R95.2
unnamed: Q32.1, U96.8
unnamed: Q32.3, U96.7
unnamed: D64.A, R96.2
unnamed: R96.1, U96.9
unnamed: D65.A, R98.2
unnamed: Q33.1, U99.8
unnamed: Q33.3, U99.7
unnamed: D66.A, R99.2
unnamed: R99.1, U99.9
unnamed: D67.A, R101.2
unnamed: Q34.1, U102.8
unnamed: Q34.3, U102.7
unnamed: D68.A, R102.2
unnamed: R102.1, U102.9
unnamed: D69.A, R104.2
unnamed: Q35.1, U105.8
unnamed: Q35.3, U105.7
unnamed: D70.A, R105.2
unnamed: R105.1, U105.9
unnamed: D71.A, R107.2
unnamed: Q36.1, U108.8
unnamed: Q36.3, U108.7
unnamed: D72.A, R108.2
unnamed: R108.1, U108.9
unnamed: D73.A, R110.2
unnamed: Q37.1, U111.8
unnamed: Q37.3, U111.7
unnamed: D74.A, R111.2
unnamed: R111.1, U111.9
unnamed: D75.A, R113.2
unnamed: Q38.1, U114.8
unnamed: Q38.3, U114.7
unnamed: D76.A, R114.2
unnamed: R114.1, U114.9
unnamed: D77.A, R116.2
unnamed: Q39.1, U117.8
unnamed: Q39.3, U117.7
unnamed: D78.A, R117.2
unnamed: R117.1, U117.9
unnamed: D79.A, R119.2
unnamed: Q40.1, U120.8
unnamed: Q40.3, U120.7
unnamed: D80.A, R120.2
unnamed: R120.1, U120.9
unnamed: D81.A, R122.2
unnamed: Q41.1, U123.8
unnamed: Q41.3, U123.7
unnamed: D82.A, R123.2
unnamed: R123.1, U123.9
unnamed: D83.A, R125.2
unnamed: Q42.1, U126.8
unnamed: Q42.3, U126.7
unnamed: D84.A, R126.2
unnamed: R126.1, U126.9
unnamed: D85.A, R128.2
unnamed: Q43.1, U129.8
unnamed: Q43.3, U129.7
unnamed: D86.A, R129.2
unnamed: R129.1, U129.9
unnamed: D87.A, R131.2
unnamed: Q44.1, U132.8
unnamed: Q44.3, U132.7
unnamed: D88.A, R132.2
unnamed: R132.1, U132.9
unnamed: D89.A, R134.2
unnamed: Q45.1, U135.8
unnamed: Q45.3, U135.7
unnamed: D90.A, R135.2
unnamed: R135.1, U135.9
unnamed: D91.A, R137.2
unnamed: Q46.1, U138.8
unnamed: Q46.3, U138.7
unnamed: D92.A, R138.2
unnamed: R138.1, U138.9
unnamed: D93.A, R140.2
unnamed: Q47.1, U141.8
unnamed: Q47.3, U141.7
unnamed: D94.A, R141.2
unnamed: R141.1, U141.9
unnamed: D95.A, R143.2
unnamed: Q48.1, U144.8
unnamed: Q48.3, U144.7
unnamed: D96.A, R144.2
unnamed: R144.1, U144.9
unnamed: D97.A, R146.2
unnamed: Q49.1, U147.8
unnamed: Q49.3, U147.7
unnamed: D98.A, R147.2
unnamed: R147.1, U147.9
unnamed: D99.A, R149.2
unnamed: Q50.1, U150.8
unnamed: Q50.3, U150.7
unnamed: D100.A, R150.2
unnamed: R150.1, U150.9
unnamed: D101.A, R152.2
unnamed: Q51.1, U153.8
unnamed: Q51.3, U153.7
unnamed: D102.A, R153.2
unnamed: R153.1, U153.9
unnamed: D103.A, R155.2
unnamed: Q52.1, U156.8
unnamed: Q52.3, U156.7
unnamed: D104.A, R156.2
unnamed: R156.1, U156.9
unnamed: D105.A, R158.2
unnamed: Q53.1, U159.8
unnamed: Q53.3, U159.7
unnamed: D106.A, R159.2
unnamed: R159.1, U159.9
unnamed: D107.A, R161.2
unnamed: Q54.1, U162.8
unnamed: Q54.3, U162.7
unnamed: D108.A, R162.2
unnamed: R162.1, U162.9
unnamed: D109.A, R164.2
unnamed: Q55.1, U165.8
unnamed: Q55.3, U165.7
unnamed: D110.A, R165.2
unnamed: R165.1, U165.9
unnamed: D111.A, R167.2
unnamed: Q56.1, U168.8
unnamed: Q56.3, U168.7
unnamed: D112.A, R168.2
unnamed: R168.1, U168.9
unnamed: D113.A, R170.2
unnamed: Q57.1, U171.8
unnamed: Q57.3, U171.7
unnamed: D114.A, R171.2
unnamed: R171.1, U171.9
unnamed: D115.A, R173.2
unnamed: Q58.1, U174.8
unnamed: Q58.3, U174.7
unnamed: D116.A, R174.2
unnamed: R174.1, U174.9
unnamed: D117.A, R176.2
unnamed: Q59.1, U177.8
unnamed: Q59.3, U177.7
unnamed: D118.A, R177.2
unnamed: R177.1, U177.9
unnamed: D119.A, R179.2
unnamed: Q60.1, U180.8
unnamed: Q60.3, U180.7
unnamed: D120.A, R180.2
unnamed: R180.1, U180.9
RAW: JP1.4, U2.1, U2.3
RAW1: JP3.4, U4.1, U4.3
RAW2: JP5.4, U7.1, U7.3
RAW3: JP7.4, U10.1, U10.3
RAW4: JP9.4, U13.1, U13.3
RAW5: JP11.4, U16.1, U16.3
RAW6: JP13.4, U19.1, U19.3
RAW7: JP15.4, U22.1, U22.3
RAW8: JP17.4, U25.1, U25.3
RAW9: JP19.4, U28.1, U28.3
RAW10: JP21.4, U31.1, U31.3
RAW11: JP23.4, U34.1, U34.3
RAW12: JP25.4, U37.1, U37.3
RAW13: JP27.4, U40.1, U40.3
RAW14: JP29.4, U43.1, U43.3
RAW15: JP31.4, U46.1, U46.3
RAW16: JP33.4, U49.1, U49.3
RAW17: JP35.4, U52.1, U52.3
RAW18: JP37.4, U55.1, U55.3
RAW19: JP39.4, U58.1, U58.3
RAW20: JP41.4, U61.1, U61.3
RAW21: JP43.4, U64.1, U64.3
RAW22: JP45.4, U67.1, U67.3
RAW23: JP47.4, U70.1, U70.3
RAW24: JP49.4, U73.1, U73.3
RAW25: JP51.4, U76.1, U76.3
RAW26: JP53.4, U79.1, U79.3
RAW27: JP55.4, U82.1, U82.3
RAW28: JP57.4, U85.1, U85.3
RAW29: JP59.4, U88.1, U88.3
RAW30: JP61.4, U91.1, U91.3
RAW31: JP63.4, U94.1, U94.3
RAW32: JP65.4, U97.1, U97.3
RAW33: JP67.4, U100.1, U100.3
RAW34: JP69.4, U103.1, U103.3
RAW35: JP71.4, U106.1, U106.3
RAW36: JP73.4, U109.1, U109.3
RAW37: JP75.4, U112.1, U112.3
RAW38: JP77.4, U115.1, U115.3
RAW39: JP79.4, U118.1, U118.3
RAW40: JP81.4, U121.1, U121.3
RAW41: JP83.4, U124.1, U124.3
RAW42: JP85.4, U127.1, U127.3
RAW43: JP87.4, U130.1, U130.3
RAW44: JP89.4, U133.1, U133.3
RAW45: JP91.4, U136.1, U136.3
RAW46: JP93.4, U139.1, U139.3
RAW47: JP95.4, U142.1, U142.3
RAW48: JP97.4, U145.1, U145.3
RAW49: JP99.4, U148.1, U148.3
RAW50: JP101.4, U151.1, U151.3
RAW51: JP103.4, U154.1, U154.3
RAW52: JP105.4, U157.1, U157.3
RAW53: JP107.4, U160.1, U160.3
RAW54: JP109.4, U163.1, U163.3
RAW55: JP111.4, U166.1, U166.3
RAW56: JP113.4, U169.1, U169.3
RAW57: JP115.4, U172.1, U172.3
RAW58: JP117.4, U175.1, U175.3
RAW59: JP119.4, U178.1, U178.3
RST: C2.1, JP2.1, R2.1, U1.29
RST1: C7.1, JP4.1, R3.1, U6.29
RST2: C11.1, JP6.1, R7.1, U9.29
RST3: C15.1, JP8.1, R10.1, U12.29
RST4: C19.1, JP10.1, R13.1, U15.29
RST5: C23.1, JP12.1, R16.1, U18.29
RST6: C27.1, JP14.1, R19.1, U21.29
RST7: C31.1, JP16.1, R22.1, U24.29
RST8: C35.1, JP18.1, R25.1, U27.29
RST9: C39.1, JP20.1, R28.1, U30.29
RST10: C43.1, JP22.1, R31.1, U33.29
RST11: C47.1, JP24.1, R34.1, U36.29
RST12: C51.1, JP26.1, R37.1, U39.29
RST13: C55.1, JP28.1, R40.1, U42.29
RST14: C59.1, JP30.1, R43.1, U45.29
RST15: C63.1, JP32.1, R46.1, U48.29
RST16: C67.1, JP34.1, R49.1, U51.29
RST17: C71.1, JP36.1, R52.1, U54.29
RST18: C75.1, JP38.1, R55.1, U57.29
RST19: C79.1, JP40.1, R58.1, U60.29
RST20: C83.1, JP42.1, R61.1, U63.29
RST21: C87.1, JP44.1, R64.1, U66.29
RST22: C91.1, JP46.1, R67.1, U69.29
RST23: C95.1, JP48.1, R70.1, U72.29
RST24: C99.1, JP50.1, R73.1, U75.29
RST25: C103.1, JP52.1, R76.1, U78.29
RST26: C107.1, JP54.1, R79.1, U81.29
RST27: C111.1, JP56.1, R82.1, U84.29
RST28: C115.1, JP58.1, R85.1, U87.29
RST29: C119.1, JP60.1, R88.1, U90.29
RST30: C123.1, JP62.1, R91.1, U93.29
RST31: C127.1, JP64.1, R94.1, U96.29
RST32: C131.1, JP66.1, R97.1, U99.29
RST33: C135.1, JP68.1, R100.1, U102.29
RST34: C139.1, JP70.1, R103.1, U105.29
RST35: C143.1, JP72.1, R106.1, U108.29
RST36: C147.1, JP74.1, R109.1, U111.29
RST37: C151.1, JP76.1, R112.1, U114.29
RST38: C155.1, JP78.1, R115.1, U117.29
RST39: C159.1, JP80.1, R118.1, U120.29
RST40: C163.1, JP82.1, R121.1, U123.29
RST41: C167.1, JP84.1, R124.1, U126.29
RST42: C171.1, JP86.1, R127.1, U129.29
RST43: C175.1, JP88.1, R130.1, U132.29
RST44: C179.1, JP90.1, R133.1, U135.29
RST45: C183.1, JP92.1, R136.1, U138.29
RST46: C187.1, JP94.1, R139.1, U141.29
RST47: C191.1, JP96.1, R142.1, U144.29
RST48: C195.1, JP98.1, R145.1, U147.29
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
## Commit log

2015-06-23 Changed c10 to c4
2015-08-03 Schematic cleanup
    Fixed four-way junction and better defined sections of sch.
2015-08-04 created panel v14
2015-08-04 Revert "created panel v14"
    This reverts commit b705ebf0a90bbcd340dfe3f8b7ac4d2d77a225cc.
2015-08-04 Adding fiducials to bottom side
    Adding fiducials to bottom side for SD card socket placement.
2015-09-01 added bottom side panel fids

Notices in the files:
parts and their libraries:
SparkFun-Connectors: Licensing: Creative Commons ShareAlike 4.0 International - https://creativecommons.org/licenses/by-sa/4.0
